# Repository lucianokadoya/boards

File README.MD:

# Meccano Boards
Meccano is a development kit based on ESP8266, integates GPIO, PWM, IIC, 1-Wire and ADC all in one board.
Different from other ESP8266 projects, Meccano board has been heavily tested in retail stores and adjusted to be safe against RF (radio frequency) interferences. The physical store is an inhospitable environment since there are several hundreds of electronic products, such as TVs, computers, sound and home theaters as well as electronic home appliances.

## Features
 - Arduino Like Hardware
 - NodeMCU
 - Low cost WiFi
 - Heavily tested
 - Open Source

 ## Meccano Hardware Platform

 ### What is the history behind Meccano Board?

 Meccano Board project started early 2014 for Magazine Luiza, leaded by Rogerio Biondi, Luciano Kadoya and Diego Osse for a Large Retailer of São Paulo/Brazil. The initial goal was collecting information about the number of the visitors in each physical store in order to calculate several productivity ratios such as the number of sales by visitors and total amount of sales by visitors. The development started using commodity hardware available on the market and the Arduino Platform was the first board choosen for development. After some rounds of development, due to the nature of the application, the Ethernet connection was discarded due to several facility issues. After that several Wi-Fi solutions were tried by the development team and none of them considered satisfatory or reliable.

 During that time the ESP8266 was presented to the market as a really cheap solution and group started a spin-off project based on that microprocessor, the ESP-01 board. But dev team quickly realized that despite the low cost and good number of features, ESP8266 was not an out-of-the-box solution without a reliable development board. It has been tried but failed due to the high intensive RF (Radio Frequency) issues in the physical store, where there are several TVs, computers, mobile phones, sound systems and other appliances sharing the same power line/system. The team has pivoted from Arduino to ESP8266 and a quick prototype has been created (Take a look at Development History), a little larger than a R$ 1,00 coin. When tested in the field, it rocked and a new board called Meccano Mini has born.

 ### Why should I use Meccano Mini Board?

 This is just a question of preference. Meccano Board is optimized for running retail IoT applications and has already been built for low cost and high scale production. Due to cost reduction, it has a simple design, uses a 5V switched font, just one tension regulator and needs a simple FTDI board for programming. Since this doesn't have many SMD components, it may also be assembled at home.

 ### How do I assemble and test my Meccano Board?

 Just download the meccano-iot/boards content and produce your own PCB (printed circuit board). One of the recommended services is OSH Park, where you may produce your PCB with high quality and low cost. Take a look at http://www.oshpark.com for more details, submit the eagle/PCB file there and produce your board. After that, you must buy the components. They are specified in detail in the components.txt file. After you have assembled it, download the client for that board (meccano-iot/arduino-esp-library), install the software (Arduino IDE, Arduino-ESP board libraries and meccano library) and deploy the sample script for testing.

## Versions
[Meccano Micro](/meccano_micro.MD)

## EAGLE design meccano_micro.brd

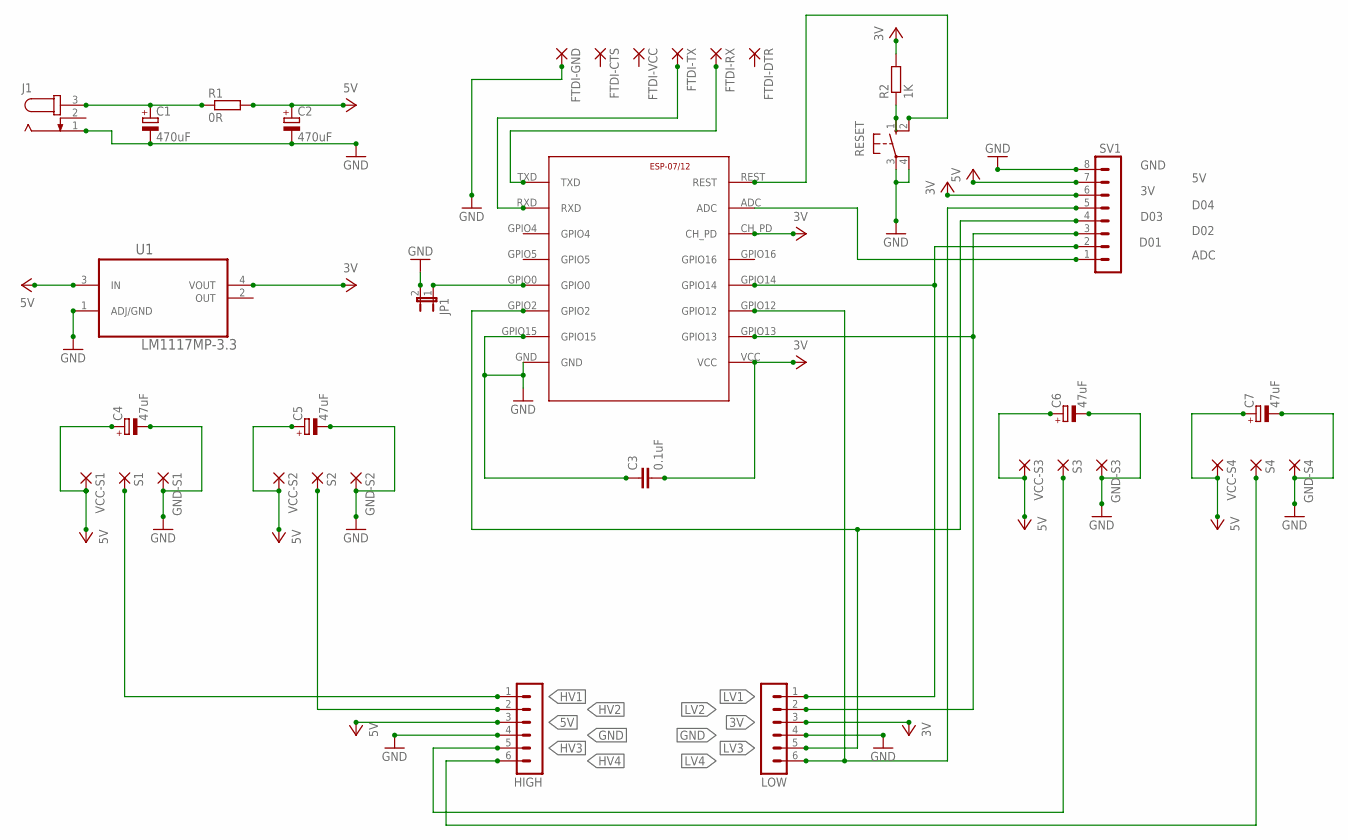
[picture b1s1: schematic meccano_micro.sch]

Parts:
C1, C2: 470uF; B45181B
C3: 0.1uF; C2.5-4
C4, C5, C6, C7: 47uF; B45181B
ESP-07/12: ESP8266-07; ESP-07
FTDI-CTS: 1,6/0,8
FTDI-DTR: 1,6/0,8
FTDI-GND: 1,6/0,8
FTDI-RX: 1,6/0,8
FTDI-TX: 1,6/0,8
FTDI-VCC: 1,6/0,8
GND-S1, GND-S2, GND-S3, GND-S4: 1,6/0,8
HIGH: MA06-1
J1: JACK-PLUG0; SPC4077
JP1: JP1E; JP1
LOW: MA06-1
R1: 0R; 0204/7
R2: 1K; 0204/7
RESET: 10-XX; B3F-10XX
S1, S2, S3, S4: 1,6/0,8
SV1: MA08-1
U1: LM1117MP-3.3; SOT230P696X180-4N
VCC-S1, VCC-S2, VCC-S3, VCC-S4: 1,6/0,8

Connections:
3V: C3.2, ESP-07/12.CH_PD, ESP-07/12.VCC, LOW.3, R2.1, R2.2, RESET.1 (S), SV1.6, U1.4 (VOUT)
5V: C2.+, C4.+, C5.+, C6.+, C7.+, HIGH.3, R1.2, SV1.7, U1.3 (IN), VCC-S1.1, VCC-S2.1, VCC-S3.1, VCC-S4.1
GND: C1.-, C2.-, C3.1, C4.-, C5.-, C6.-, C7.-, ESP-07/12.GND, ESP-07/12.GPIO15, FTDI-GND.1, GND-S1.1, GND-S2.1, GND-S3.1, GND-S4.1, HIGH.4, J1.1, JP1.2, LOW.4, RESET.3, RESET.4 (P1), SV1.8, U1.1 (ADJ/GND)
HV1: HIGH.1, S1.1
HV2: HIGH.2, S2.1
HV3: HIGH.5, S3.1
HV4: HIGH.6, S4.1
LV1: ESP-07/12.GPIO14, LOW.1, SV1.2
LV2: ESP-07/12.GPIO13, LOW.2, SV1.3
LV3: ESP-07/12.GPIO2, LOW.5, SV1.4
LV4: ESP-07/12.GPIO12, LOW.6, SV1.5
unnamed: C1.+, J1.3, R1.1
unnamed: ESP-07/12.ADC, SV1.1
unnamed: ESP-07/12.GPIO0, JP1.1
unnamed: ESP-07/12.RXD, FTDI-TX.1
unnamed: ESP-07/12.TXD, FTDI-RX.1
unnamed: ESP-07/12.REST, RESET.2 (S1)

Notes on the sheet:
D04
D03
D02
D01
ADC

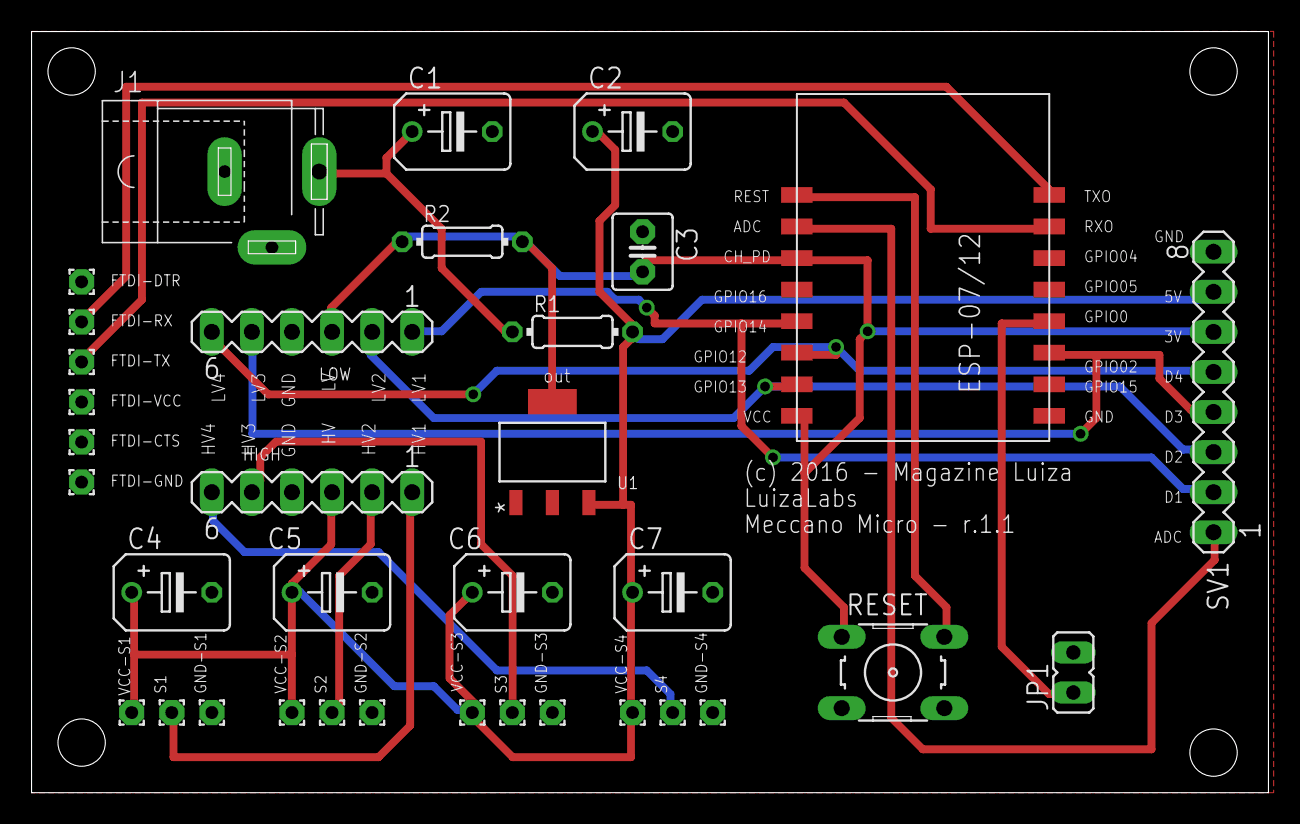
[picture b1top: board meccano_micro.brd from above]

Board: 2 copper layers, 78.4 x 48.2 mm, 35 parts (0 on the bottom side), 17 nets.

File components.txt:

1 x ESP8266 Serial WiFi Module (ESP-07/ESP-12)
1 x SparkFun Logic Level Converter - Bi-Directional (https://www.sparkfun.com/products/12009 or https://www.robocore.net/modules.php?name=GR_LojaVirtual&prod=522)
1 x IC LM1117MPX-3.3V STO-223
4 x Electrolytic Capacitor 47uF/16V
2 x Electrolytic Capacitor 470uF/16V
1 x Ceramic Capacitor Disc 100Kpf/50V (104/100K/100nF/0.1uF) 
1 x Resistor 1/4 Watt CR25 5% - 0 Ohm
1 x Resistor 1/4 Watt CR25 5% - 1K Ohm
1 x Jumper 2 Pins to PCI 
1 x JACK-PLUG0 (JACK-PLUG)
1 x Mini Pushbutton Switch NC
1 x Female Headers
1 x Male Headers

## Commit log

2016-01-04 Init
2016-01-04 Link Fix
2016-01-04 pin labels fix and added pinout documentation.
    Changed pin labels “S(1,2,3,4)” to “D(01,02,03,04)”
2016-02-04 Update board designer
2016-02-16 Component List
2016-02-16 Documentation
2016-02-16 Image links fixed
2016-02-16 Image link fix
2016-03-11 Fix Configuration and Logical GPIO components

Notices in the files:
meccano_micro.brd:
(c) 2016 - Magazine Luiza
